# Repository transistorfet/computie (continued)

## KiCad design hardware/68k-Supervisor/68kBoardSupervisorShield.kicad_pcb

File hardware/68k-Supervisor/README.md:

68k-Supervisor
==============

Status: Built & Tested

Latest: Rev.2

### About
An arduino shield for the Arduino Mega 2560 with two 40-pin connectors that match the two 40-pin
expansion headers of the computie single board computers (68k-SBC, 68k-SMT, and k30-SBC with
rework).

### 68k-SBC and 68k-SMT

Use the [68kSupervisor](../../software/arduino/68kSupervisor) sketch to program the flash
in-circuit, debug the CPU, or host memory and serial I/O access via the memory bus.  Make sure to
set the 68k-* board jumpers correctly for DTACK and the RAM location if debugging or hosting with
the supervisor.

### k30-SBC

This PCB requires some changes before it can be used with the k30-SBC:
    - Address 0 on the ADBUS 40-pin connector (Pin 39) should be wired to Digital Input #9 (D9) of the
      Arudino
    - the WR pin on the SIGBUS 40-pin connector (Pin 14) should be wired to Digital Input #8 of the
      Arudino (D8).  It was a duplicate of R/W on the 68k-* boards, but it's now the DS (data strobe)
      signal from the 68030 on the k30-SBC
The [k30FlashWriter](../../software/arduino/k30FlashWriter) sketch should be used, which will only
allow running or suspending the CPU, and writing to the flash chip in-circuit to bootstrap the
board.  The debugging feature has been removed since it didn't work correctly at the 12MHz speed
that the 68030 is running at.  The k30 board only has one 512kB of flash in a single 8-bit wide
chip, instead of two flash chips in parallel to fit the 16-bit interface of the 68010 that the 68k-*
boards have, which is why this alternate flash writing sketch is needed.  The reworked shield can
still work with the 68kSupervisor sketch to communicate with the 68k-* boards.

[Revision 2 Schematic](revisions/68kBoardSupervisorShield-rev2.pdf)

[Revision 2 Gerbers](revisions/68kBoardSupervisorShield-rev2.zip)

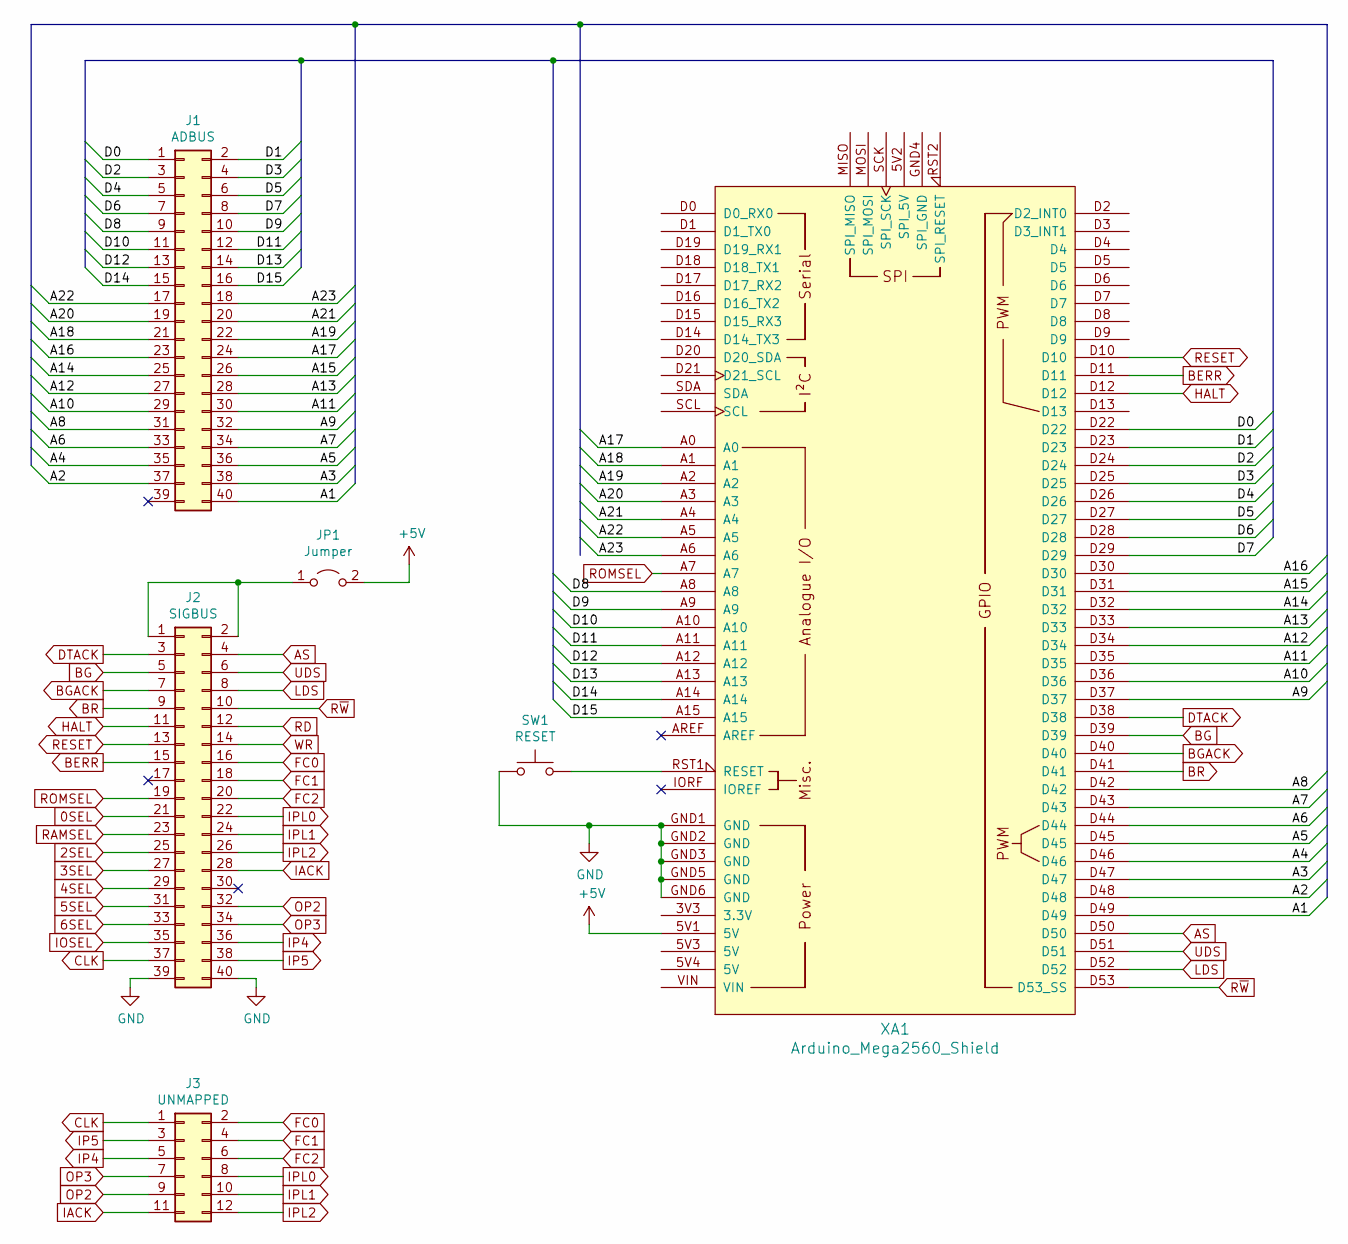
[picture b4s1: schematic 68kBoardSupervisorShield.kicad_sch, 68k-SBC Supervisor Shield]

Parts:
J1: ADBUS; PinHeader_2x20_P2.54mm_Vertical
J2: SIGBUS; PinHeader_2x20_P2.54mm_Vertical
J3: UNMAPPED; PinHeader_2x06_P2.54mm_Vertical
JP1: Jumper; PinHeader_1x02_P2.54mm_Vertical
SW1: RESET; SW_PUSH_6mm
XA1: Arduino_Mega2560_Shield

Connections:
0SEL: J2.21
2SEL: J2.25
3SEL: J2.27
4SEL: J2.29
5SEL: J2.31
6SEL: J2.33
+5V: JP1.2 (B), XA1.5V1 (5V)
/A1: J1.40, XA1.D49
/A2: J1.37, XA1.D48
/A3: J1.38, XA1.D47
/A4: J1.35, XA1.D46
/A5: J1.36, XA1.D45
/A6: J1.33, XA1.D44
/A7: J1.34, XA1.D43
/A8: J1.31, XA1.D42
/A9: J1.32, XA1.D37
/A10: J1.29, XA1.D36
/A11: J1.30, XA1.D35
/A12: J1.27, XA1.D34
/A13: J1.28, XA1.D33
/A14: J1.25, XA1.D32
/A15: J1.26, XA1.D31
/A16: J1.23, XA1.D30
/A17: J1.24, XA1.A0
/A18: J1.21, XA1.A1
/A19: J1.22, XA1.A2
/A20: J1.19, XA1.A3
/A21: J1.20, XA1.A4
/A22: J1.17, XA1.A5
/A23: J1.18, XA1.A6
/D0: J1.1, XA1.D22
/D1: J1.2, XA1.D23
/D2: J1.3, XA1.D24
/D3: J1.4, XA1.D25
/D4: J1.5, XA1.D26
/D5: J1.6, XA1.D27
/D6: J1.7, XA1.D28
/D7: J1.8, XA1.D29
/D8: J1.9, XA1.A8
/D9: J1.10, XA1.A9
/D10: J1.11, XA1.A10
/D11: J1.12, XA1.A11
/D12: J1.13, XA1.A12
/D13: J1.14, XA1.A13
/D14: J1.15, XA1.A14
/D15: J1.16, XA1.A15
AS: J2.4, XA1.D50
BERR: J2.15, XA1.D11
BG: J2.5, XA1.D39
BGACK: J2.7, XA1.D40
BR: J2.9, XA1.D41
CLK: J2.37, J3.1
DTACK: J2.3, XA1.D38
FC0: J2.16, J3.2
FC1: J2.18, J3.4
FC2: J2.20, J3.6
GND: J2.39, J2.40, SW1.1, XA1.GND1 (GND), XA1.GND2 (GND), XA1.GND3 (GND), XA1.GND5 (GND), XA1.GND6 (GND)
HALT: J2.11, XA1.D12
IACK: J2.28, J3.11
IOSEL: J2.35
IP4: J2.36, J3.5
IP5: J2.38, J3.3
IPL0: J2.22, J3.8
IPL1: J2.24, J3.10
IPL2: J2.26, J3.12
LDS: J2.8, XA1.D52
unnamed: J2.1, J2.2, JP1.1 (A)
unnamed: SW1.2, XA1.RST1 (RESET)
OP2: J2.32, J3.9
OP3: J2.34, J3.7
RAMSEL: J2.23
RD: J2.12
RESET: J2.13, XA1.D10
ROMSEL: J2.19, XA1.A7
R~W: J2.10, XA1.D53 (D53_SS)
UDS: J2.6, XA1.D51
WR: J2.14

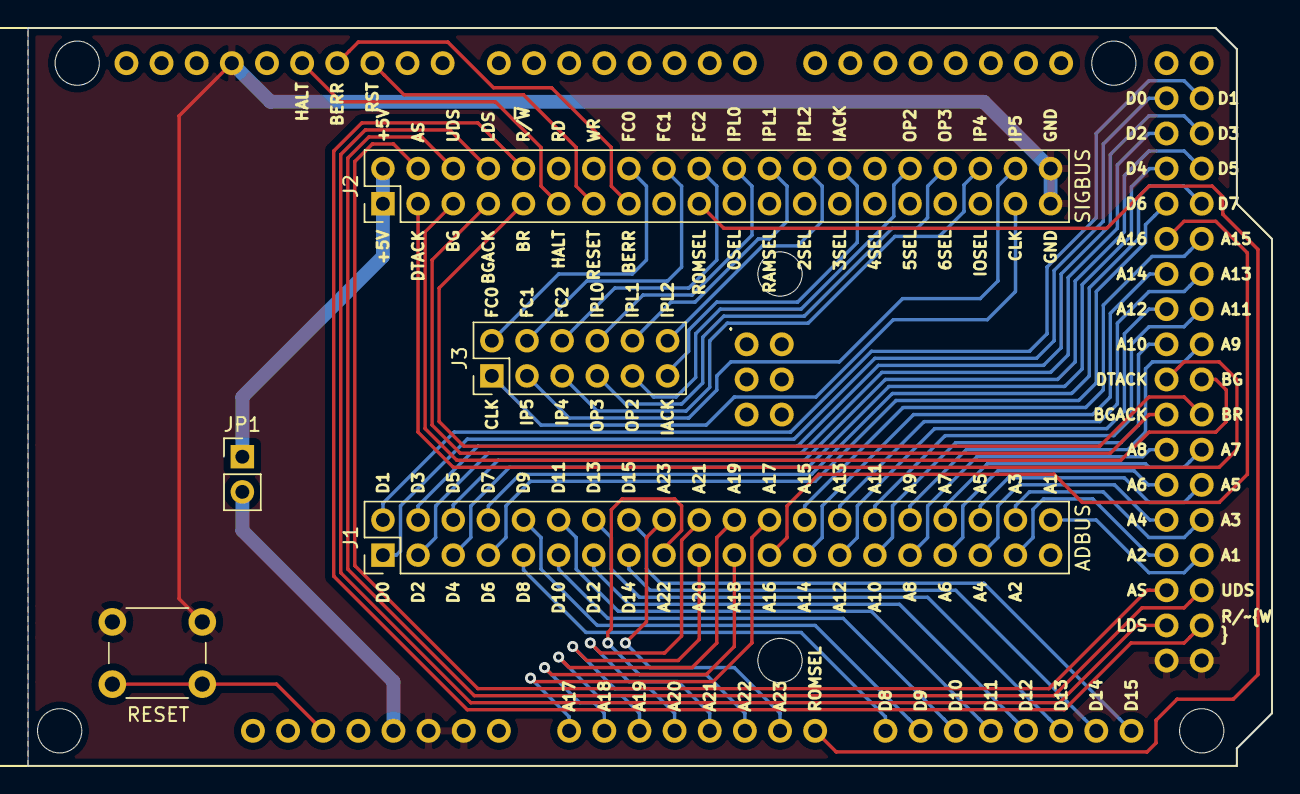
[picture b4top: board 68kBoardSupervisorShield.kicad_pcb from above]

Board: 2 copper layers, 89.9 x 53.3 mm, 6 parts (0 on the bottom side), 67 nets.

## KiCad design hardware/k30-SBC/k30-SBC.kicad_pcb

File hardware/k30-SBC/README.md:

k30-SBC
=======

Status: Built & Tested

Latest: Rev.2

### About
A single board computer with DIP packaged chips.  The only programmable chip is the flash memory, which can
be written in-circuit using the Ardunio-based supervisor shield.

[Revision 2 Notes & Errata](revisions/k30-SBC-rev2-errata.txt)

[Revision 2 Schematic](revisions/k30-SBC-rev2.pdf)

[Revision 2 Gerbers](revisions/k30-SBC-rev2.zip)

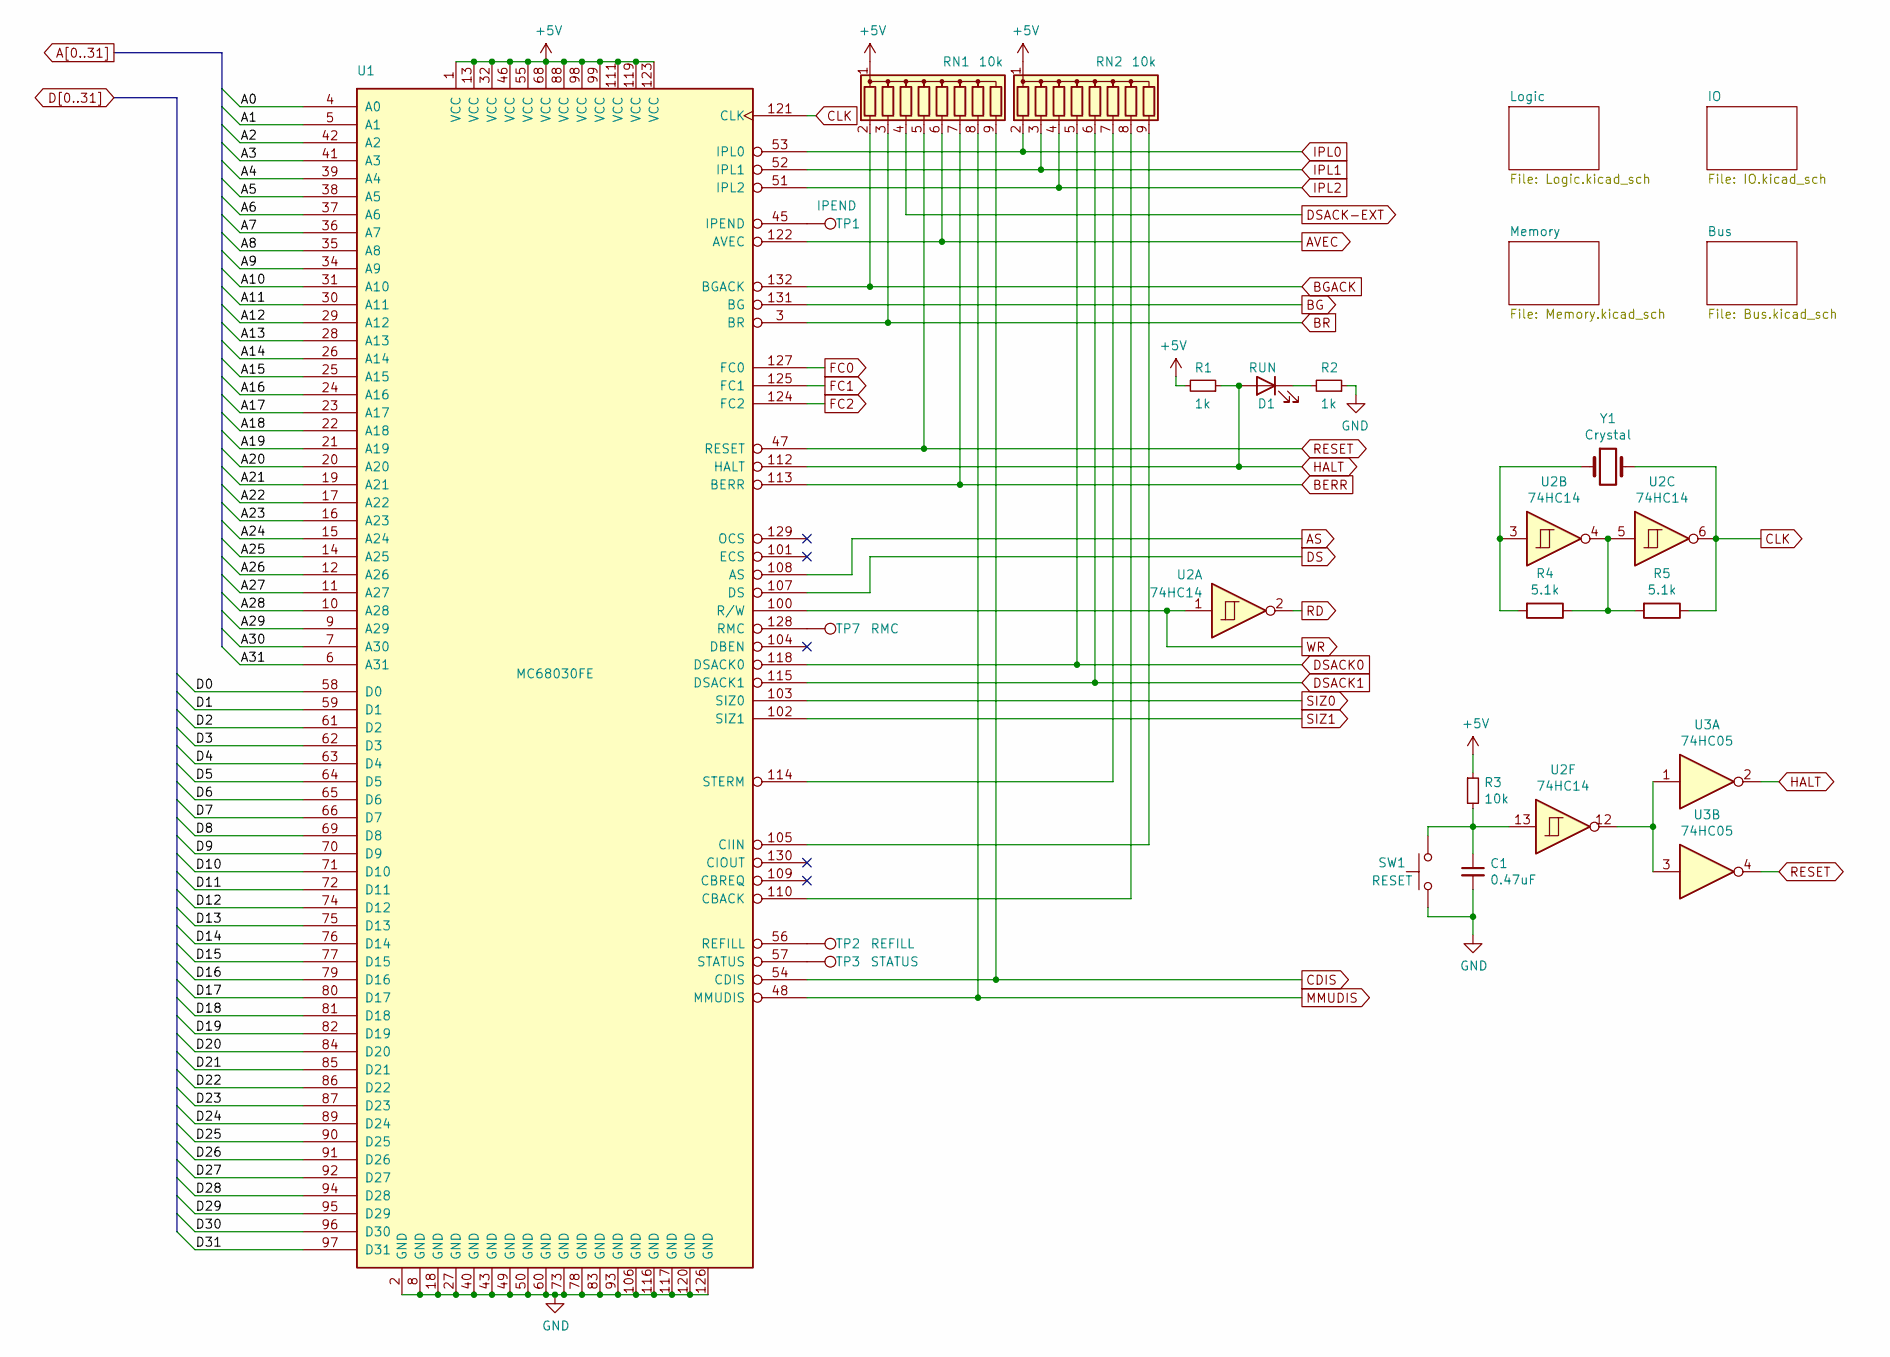
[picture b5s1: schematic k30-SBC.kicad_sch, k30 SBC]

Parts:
C1: 0.47uF; C_Disc_D3.0mm_W2.0mm_P2.50mm
D1: RUN; LED_D5.0mm
R1, R2: 1k; R_Axial_DIN0204_L3.6mm_D1.6mm_P5.08mm_Horizontal
R3: 10k; R_Axial_DIN0204_L3.6mm_D1.6mm_P5.08mm_Horizontal
R4, R5: 5.1k; R_Axial_DIN0204_L3.6mm_D1.6mm_P5.08mm_Horizontal
RN1, RN2: 10k; R_Array_SIP9
SW1: RESET; SW_PUSH_6mm
TP1: IPEND; TestPoint_THTPad_2.0x2.0mm_Drill1.0mm
TP2: REFILL; TestPoint_THTPad_2.0x2.0mm_Drill1.0mm
TP3: STATUS; TestPoint_THTPad_2.0x2.0mm_Drill1.0mm
TP7: RMC; TestPoint_THTPad_2.0x2.0mm_Drill1.0mm
U1: MC68030FE; PQFP-132_24x24mm_P0.635mm
U2: 74HC14; TSSOP-14_4.4x5mm_P0.65mm
U3: 74HC05; TSSOP-14_4.4x5mm_P0.65mm
Y1: Crystal; Crystal_HC49-4H_Vertical

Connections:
+5V: R1.2, R3.1, RN1.1 (common), RN2.1 (common), U1.1 (VCC), U1.13 (VCC), U1.32 (VCC), U1.46 (VCC), U1.55 (VCC), U1.68 (VCC), U1.88 (VCC), U1.98 (VCC), U1.99 (VCC), U1.111 (VCC), U1.119 (VCC), U1.123 (VCC); also elsewhere on the board
A0: U1.4 (A0); also elsewhere on the board
A1: U1.5 (A1); also elsewhere on the board
A2: U1.42 (A2); also elsewhere on the board
A3: U1.41 (A3); also elsewhere on the board
A4: U1.39 (A4); also elsewhere on the board
A5: U1.38 (A5); also elsewhere on the board
A6: U1.37 (A6); also elsewhere on the board
A7: U1.36 (A7); also elsewhere on the board
A8: U1.35 (A8); also elsewhere on the board
A9: U1.34 (A9); also elsewhere on the board
A10: U1.31 (A10); also elsewhere on the board
A11: U1.30 (A11); also elsewhere on the board
A12: U1.29 (A12); also elsewhere on the board
A13: U1.28 (A13); also elsewhere on the board
A14: U1.26 (A14); also elsewhere on the board
A15: U1.25 (A15); also elsewhere on the board
A16: U1.24 (A16); also elsewhere on the board
A17: U1.23 (A17); also elsewhere on the board
A18: U1.22 (A18); also elsewhere on the board
A19: U1.21 (A19); also elsewhere on the board
A20: U1.20 (A20); also elsewhere on the board
A21: U1.19 (A21); also elsewhere on the board
A22: U1.17 (A22); also elsewhere on the board
A23: U1.16 (A23); also elsewhere on the board
A24: U1.15 (A24); also elsewhere on the board
A25: U1.14 (A25); also elsewhere on the board
A26: U1.12 (A26); also elsewhere on the board
A27: U1.11 (A27); also elsewhere on the board
A28: U1.10 (A28); also elsewhere on the board
A29: U1.9 (A29); also elsewhere on the board
A30: U1.7 (A30); also elsewhere on the board
A31: U1.6 (A31); also elsewhere on the board
AS: U1.108 (AS); also elsewhere on the board
AVEC: RN1.6 (R5), U1.122 (AVEC); also elsewhere on the board
BERR: RN1.7 (R6), U1.113 (BERR); also elsewhere on the board
BG: U1.131 (BG); also elsewhere on the board
BGACK: RN1.2 (R1), U1.132 (BGACK); also elsewhere on the board
BR: RN1.3 (R2), U1.3 (BR); also elsewhere on the board
CDIS: RN1.9 (R8), U1.54 (CDIS); also elsewhere on the board
CLK: R5.1, U1.121 (CLK), U2.6, Y1.2; also elsewhere on the board
D0: U1.58 (D0); also elsewhere on the board
D1: U1.59 (D1); also elsewhere on the board
D2: U1.61 (D2); also elsewhere on the board
D3: U1.62 (D3); also elsewhere on the board
D4: U1.63 (D4); also elsewhere on the board
D5: U1.64 (D5); also elsewhere on the board
D6: U1.65 (D6); also elsewhere on the board
D7: U1.66 (D7); also elsewhere on the board
D8: U1.69 (D8); also elsewhere on the board
D9: U1.70 (D9); also elsewhere on the board
D10: U1.71 (D10); also elsewhere on the board
D11: U1.72 (D11); also elsewhere on the board
D12: U1.74 (D12); also elsewhere on the board
D13: U1.75 (D13); also elsewhere on the board
D14: U1.76 (D14); also elsewhere on the board
D15: U1.77 (D15); also elsewhere on the board
D16: U1.79 (D16); also elsewhere on the board
D17: U1.80 (D17); also elsewhere on the board
D18: U1.81 (D18); also elsewhere on the board
D19: U1.82 (D19); also elsewhere on the board
D20: U1.84 (D20); also elsewhere on the board
D21: U1.85 (D21); also elsewhere on the board
D22: U1.86 (D22); also elsewhere on the board
D23: U1.87 (D23); also elsewhere on the board
D24: U1.89 (D24); also elsewhere on the board
D25: U1.90 (D25); also elsewhere on the board
D26: U1.91 (D26); also elsewhere on the board
D27: U1.92 (D27); also elsewhere on the board
D28: U1.94 (D28); also elsewhere on the board
D29: U1.95 (D29); also elsewhere on the board
D30: U1.96 (D30); also elsewhere on the board
D31: U1.97 (D31); also elsewhere on the board
DS: U1.107 (DS); also elsewhere on the board
DSACK0: RN2.5 (R4), U1.118 (DSACK0); also elsewhere on the board
DSACK1: RN2.6 (R5), U1.115 (DSACK1); also elsewhere on the board
DSACK-EXT: RN1.4 (R3); also elsewhere on the board
FC0: U1.127 (FC0); also elsewhere on the board
FC1: U1.125 (FC1); also elsewhere on the board
FC2: U1.124 (FC2); also elsewhere on the board
GND: C1.2, R2.1, SW1.1, U1.2 (GND), U1.8 (GND), U1.18 (GND), U1.27 (GND), U1.40 (GND), U1.43 (GND), U1.49 (GND), U1.50 (GND), U1.60 (GND), U1.73 (GND), U1.78 (GND), U1.83 (GND), U1.93 (GND), U1.106 (GND), U1.116 (GND), U1.117 (GND), U1.120 (GND), U1.126 (GND); also elsewhere on the board
HALT: D1.2 (A), R1.1, U1.112 (HALT), U3.2; also elsewhere on the board
IPL0: RN2.2 (R1), U1.53 (IPL0); also elsewhere on the board
IPL1: RN2.3 (R2), U1.52 (IPL1); also elsewhere on the board
IPL2: RN2.4 (R3), U1.51 (IPL2); also elsewhere on the board
MMUDIS: RN1.8 (R7), U1.48 (MMUDIS); also elsewhere on the board
unnamed: C1.1, R3.2, SW1.2, U2.13
unnamed: D1.1 (K), R2.2
unnamed: R4.1, R5.2, U2.4, U2.5
unnamed: R4.2, U2.3, Y1.1
unnamed: RN2.7 (R6), U1.114 (STERM)
unnamed: RN2.8 (R7), U1.110 (CBACK)
unnamed: RN2.9 (R8), U1.105 (CIIN)
unnamed: TP1.1, U1.45 (IPEND)
unnamed: TP2.1, U1.56 (REFILL)
unnamed: TP3.1, U1.57 (STATUS)
unnamed: TP7.1, U1.128 (RMC)
unnamed: U2.12, U3.1, U3.3
RD: U2.2; also elsewhere on the board
SIZ0: U1.103 (SIZ0); also elsewhere on the board
SIZ1: U1.102 (SIZ1); also elsewhere on the board
WR: U1.100 (R/W), U2.1; also elsewhere on the board

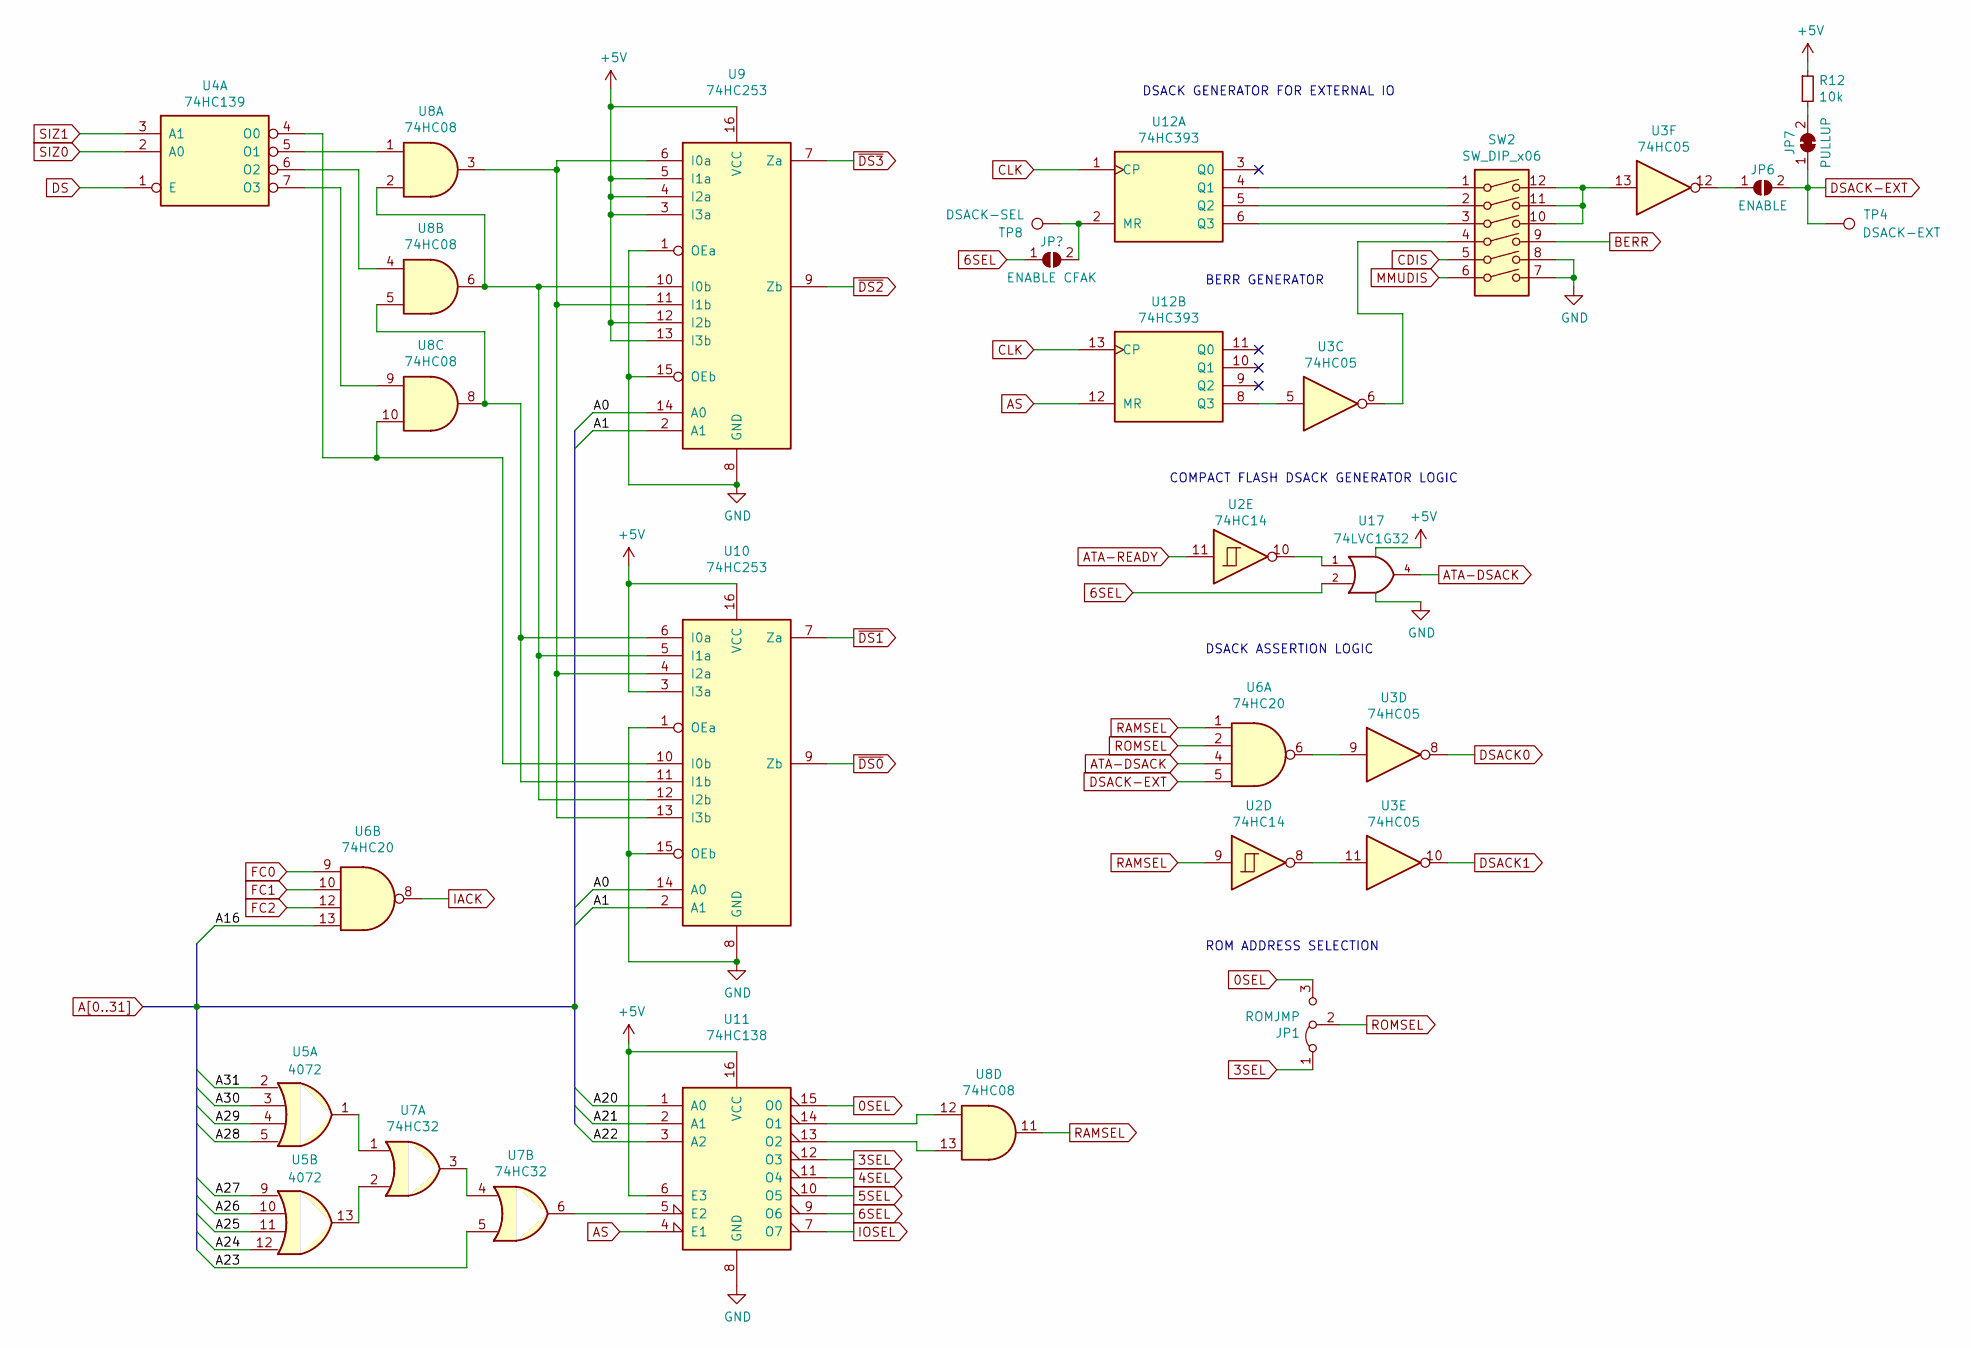
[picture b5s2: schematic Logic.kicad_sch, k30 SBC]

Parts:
JP1: ROMJMP; PinHeader_1x03_P2.54mm_Vertical
JP6: ENABLE; SolderJumper-2_P1.3mm_Open_RoundedPad1.0x1.5mm
JP7: PULLUP; SolderJumper-2_P1.3mm_Bridged_RoundedPad1.0x1.5mm
R12: 10k; R_Axial_DIN0204_L3.6mm_D1.6mm_P5.08mm_Horizontal
SW2: SW_DIP_x06; DIP-12_W7.62mm_LongPads
TP4: DSACK-EXT; TestPoint_THTPad_2.0x2.0mm_Drill1.0mm
TP8: DSACK-SEL; TestPoint_THTPad_2.0x2.0mm_Drill1.0mm
U2: 74HC14; TSSOP-14_4.4x5mm_P0.65mm
U3: 74HC05; TSSOP-14_4.4x5mm_P0.65mm
U4: 74HC139; TSSOP-16_4.4x5mm_P0.65mm
U5: 4072; TSSOP-14_4.4x5mm_P0.65mm
U6: 74HC20; TSSOP-14_4.4x5mm_P0.65mm
U7: 74HC32; TSSOP-14_4.4x5mm_P0.65mm
U8: 74HC08; TSSOP-14_4.4x5mm_P0.65mm
U9, U10: 74HC253; SSOP-16_5.3x6.2mm_P0.65mm
U11: 74HC138; TSSOP-16_4.4x5mm_P0.65mm
U12: 74HC393; TSSOP-14_4.4x5mm_P0.65mm
U17: 74LVC1G32; SOT-353_SC-70-5_Handsoldering

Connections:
0SEL: JP1.3 (B), U11.15 (O0); also elsewhere on the board
3SEL: JP1.1 (A), U11.12 (O3); also elsewhere on the board
4SEL: U11.11 (O4); also elsewhere on the board
5SEL: U11.10 (O5); also elsewhere on the board
6SEL: TP8.1, U11.9 (O6), U12.2 (MR), U17.2; also elsewhere on the board
+5V: R12.1, U9.3 (I3a), U9.4 (I2a), U9.5 (I1a), U9.12 (I2b), U9.13 (I3b), U9.16 (VCC), U10.3 (I3a), U10.16 (VCC), U11.6 (E3), U11.16 (VCC), U17.5 (VCC); also elsewhere on the board
A0: U9.14 (A0), U10.14 (A0); also elsewhere on the board
A1: U9.2 (A1), U10.2 (A1); also elsewhere on the board
A16: U6.13; also elsewhere on the board
A20: U11.1 (A0); also elsewhere on the board
A21: U11.2 (A1); also elsewhere on the board
A22: U11.3 (A2); also elsewhere on the board
A23: U7.5; also elsewhere on the board
A24: U5.12; also elsewhere on the board
A25: U5.11; also elsewhere on the board
A26: U5.10; also elsewhere on the board
A27: U5.9; also elsewhere on the board
A28: U5.5; also elsewhere on the board
A29: U5.4; also elsewhere on the board
A30: U5.3; also elsewhere on the board
A31: U5.2; also elsewhere on the board
AS: U11.4 (E1), U12.12 (MR); also elsewhere on the board
BERR: SW2.9; also elsewhere on the board
CDIS: SW2.5; also elsewhere on the board
CLK: U12.1 (CP), U12.13 (CP); also elsewhere on the board
DS: U4.1 (E); also elsewhere on the board
DSACK0: U3.8; also elsewhere on the board
DSACK1: U3.10; also elsewhere on the board
DSACK-EXT: JP6.2 (B), JP7.1 (A), TP4.1, U6.5; also elsewhere on the board
FC0: U6.9; also elsewhere on the board
FC1: U6.10; also elsewhere on the board
FC2: U6.12; also elsewhere on the board
GND: SW2.7, SW2.8, U9.1 (OEa), U9.8 (GND), U9.15 (OEb), U10.1 (OEa), U10.8 (GND), U10.15 (OEb), U11.8 (GND), U17.3 (GND); also elsewhere on the board
IACK: U6.8; also elsewhere on the board
IOSEL: U11.7 (O7); also elsewhere on the board
MMUDIS: SW2.6; also elsewhere on the board
unnamed: JP6.1 (A), U3.12
unnamed: JP7.2 (B), R12.2
unnamed: SW2.1, U12.4 (Q1)
unnamed: SW2.2, U12.5 (Q2)
unnamed: SW2.3, U12.6 (Q3)
unnamed: SW2.4, U3.6
unnamed: U2.8, U3.11
unnamed: U3.9, U6.6
unnamed: U4.5 (O1), U8.1
unnamed: U4.6 (O2), U8.4
unnamed: U4.7 (O3), U8.9
unnamed: U5.1, U7.1
unnamed: U5.13, U7.2
unnamed: U7.3, U7.4
unnamed: U4.4 (O0), U8.10, U10.10 (I0b)
unnamed: U8.5, U8.8, U10.6 (I0a), U10.11 (I1b)
unnamed: U8.2, U8.6, U9.10 (I0b), U10.5 (I1a), U10.12 (I2b)
unnamed: U8.3, U9.6 (I0a), U9.11 (I1b), U10.4 (I2a), U10.13 (I3b)
unnamed: U7.6, U11.5 (E2)
unnamed: U8.13, U11.13 (O2)
unnamed: U8.12, U11.14 (O1)
unnamed: U3.5, U12.8 (Q3)
unnamed: U2.10, U17.1
RAMSEL: U2.9, U6.1, U8.11; also elsewhere on the board
ROMSEL: JP1.2 (C), U6.2; also elsewhere on the board
SIZ0: U4.2 (A0); also elsewhere on the board
SIZ1: U4.3 (A1); also elsewhere on the board
~DS0: U10.9 (Zb); also elsewhere on the board
~DS1: U10.7 (Za); also elsewhere on the board
~DS2: U9.9 (Zb); also elsewhere on the board
~DS3: U9.7 (Za); also elsewhere on the board

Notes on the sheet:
DSACK ASSERTION LOGIC
DSACK GENERATOR FOR EXTERNAL IO
BERR GENERATOR
COMPACT FLASH DSACK GENERATOR LOGIC
ROM ADDRESS SELECTION

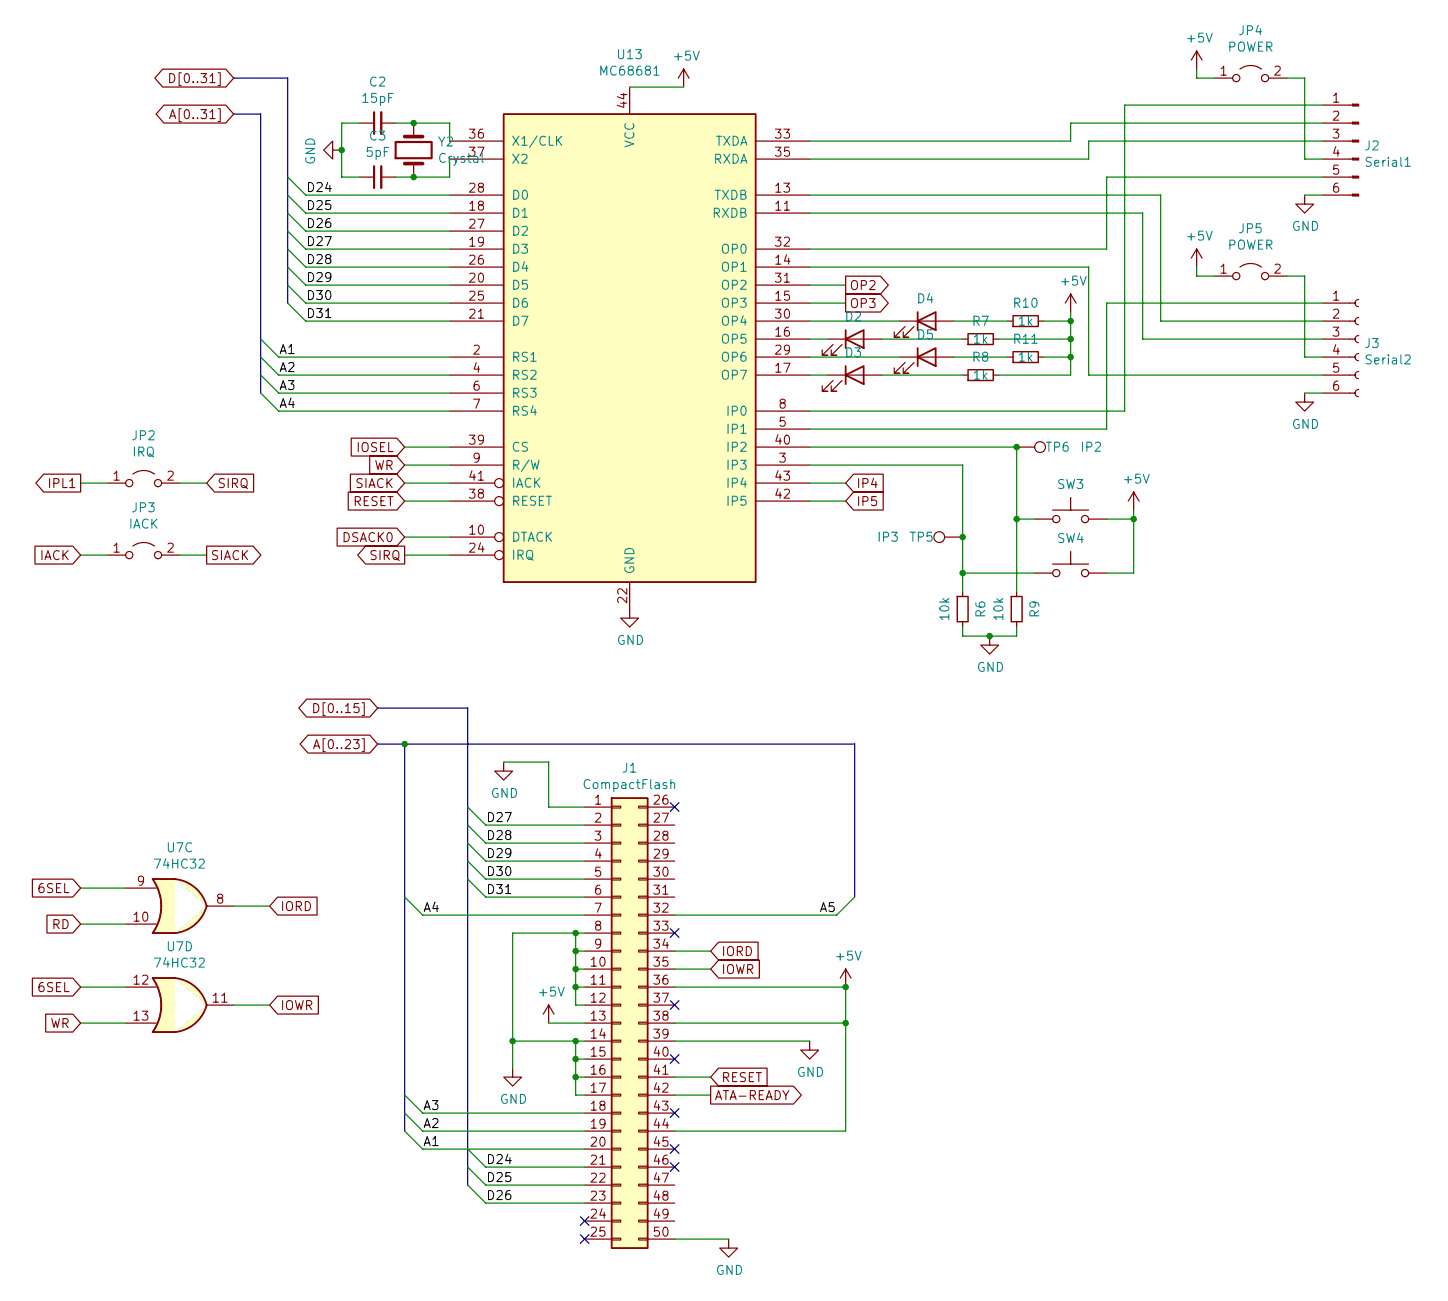
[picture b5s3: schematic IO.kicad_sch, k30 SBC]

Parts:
C2: 15pF; C_Disc_D3.0mm_W2.0mm_P2.50mm
C3: 5pF; C_Disc_D3.0mm_W2.0mm_P2.50mm
D2: OP5; LED_D5.0mm
D3: OP7; LED_D5.0mm
D4: OP4; LED_D5.0mm
D5: OP6; LED_D5.0mm
J1: CompactFlash; CF-Card_3M_N7E50-Q516RB-40
J2: Serial1; PinHeader_1x06_P2.54mm_Vertical
J3: Serial2; PinHeader_1x06_P2.54mm_Vertical
JP2: IRQ; PinHeader_1x02_P2.54mm_Vertical
JP3: IACK; PinHeader_1x02_P2.54mm_Vertical
JP4, JP5: POWER; PinHeader_1x02_P2.54mm_Vertical
R6, R9: 10k; R_Axial_DIN0204_L3.6mm_D1.6mm_P5.08mm_Horizontal
R7, R8, R10, R11: 1k; R_Axial_DIN0204_L3.6mm_D1.6mm_P5.08mm_Horizontal
SW3: IP2; SW_PUSH_6mm
SW4: IP3; SW_PUSH_6mm
TP5: IP3; TestPoint_THTPad_2.0x2.0mm_Drill1.0mm
TP6: IP2; TestPoint_THTPad_2.0x2.0mm_Drill1.0mm
U7: 74HC32; TSSOP-14_4.4x5mm_P0.65mm
U13: MC68681; PLCC-44_THT-Socket
Y2: Crystal; Crystal_HC49-4H_Vertical

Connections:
6SEL: U7.9, U7.12; also elsewhere on the board
+5V: J1.13, J1.36, J1.38, J1.44, JP4.1 (A), JP5.1 (A), R7.2, R8.2, R10.2, R11.2, SW3.2, SW4.2, U13.44 (VCC); also elsewhere on the board
A1: J1.20, U13.2 (RS1); also elsewhere on the board
A2: J1.19, U13.4 (RS2); also elsewhere on the board
A3: J1.18, U13.6 (RS3); also elsewhere on the board
A4: J1.7, U13.7 (RS4); also elsewhere on the board
A5: J1.32; also elsewhere on the board
D24: J1.21, U13.28 (D0); also elsewhere on the board
D25: J1.22, U13.18 (D1); also elsewhere on the board
D26: J1.23, U13.27 (D2); also elsewhere on the board
D27: J1.2, U13.19 (D3); also elsewhere on the board
D28: J1.3, U13.26 (D4); also elsewhere on the board
D29: J1.4, U13.20 (D5); also elsewhere on the board
D30: J1.5, U13.25 (D6); also elsewhere on the board
D31: J1.6, U13.21 (D7); also elsewhere on the board
DSACK0: U13.10 (DTACK); also elsewhere on the board
GND: C2.1, C3.1, J1.1, J1.8, J1.9, J1.10, J1.11, J1.12, J1.14, J1.15, J1.16, J1.17, J1.39, J1.50, J2.6, J3.6, R6.2, R9.2, U13.22 (GND); also elsewhere on the board
IACK: JP3.1 (A); also elsewhere on the board
IORD: J1.34, U7.8
IOSEL: U13.39 (CS); also elsewhere on the board
IOWR: J1.35, U7.11
IP4: U13.43 (IP4); also elsewhere on the board
IP5: U13.42 (IP5); also elsewhere on the board
IPL1: JP2.1 (A); also elsewhere on the board
unnamed: C2.2, U13.36 (X1/CLK), Y2.2
unnamed: C3.2, U13.37 (X2), Y2.1
unnamed: D2.1 (K), U13.16 (OP5)
unnamed: D2.2 (A), R7.1
unnamed: D3.1 (K), U13.17 (OP7)
unnamed: D3.2 (A), R8.1
unnamed: D4.1 (K), U13.30 (OP4)
unnamed: D4.2 (A), R10.1
unnamed: D5.1 (K), U13.29 (OP6)
unnamed: D5.2 (A), R11.1
unnamed: J2.1, U13.8 (IP0)
unnamed: J2.2, U13.33 (TXDA)
unnamed: J2.3, U13.35 (RXDA)
unnamed: J2.4, JP4.2 (B)
unnamed: J2.5, U13.32 (OP0)
unnamed: J3.1, U13.5 (IP1)
unnamed: J3.2, U13.13 (TXDB)
unnamed: J3.3, U13.11 (RXDB)
unnamed: J3.4, JP5.2 (B)
unnamed: J3.5, U13.14 (OP1)
unnamed: R6.1, SW4.1, TP5.1, U13.3 (IP3)
unnamed: R9.1, SW3.1, TP6.1, U13.40 (IP2)
OP2: U13.31 (OP2); also elsewhere on the board
OP3: U13.15 (OP3); also elsewhere on the board
RD: U7.10; also elsewhere on the board
SIACK: JP3.2 (B), U13.41 (IACK)
SIRQ: JP2.2 (B), U13.24 (IRQ)
WR: U7.13, U13.9 (R/W); also elsewhere on the board
